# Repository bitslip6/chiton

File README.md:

# Chiton · Wide-Angle 940 nm Time-of-Flight Sensor for Autonomous Mobile Robots

[See the application](#see-the-application) · [Engineering highlights](#engineering-highlights) · [Run it locally](#run-on-your-desktop)

Chiton controls and processes data from the **Chiton 8-vixel, 940 nm
Time-of-Flight camera**: **270° coverage, VGA (640 × 480), and 30 fps**.
The application combines sensor control, on-device processing, live visualization,
measurements, and data export. The camera serves the browser interface directly.

Chiton runs on embedded Linux and uses C++ for camera SDK integration, image
processing, and network services. Build tools, automated tests, and deployment
bundles support development from the desktop to the camera.

*Color-mapped depth view. Colors represent distance across the scene.
Select any screenshot to view it at full size.*

## Camera platform

The camera platform combines an **i.MX8 system-on-module**, a **Sony CMOS image sensor**, and an **Analog Devices (ADI)
Time-of-Flight ASIC**. ToF imaging measures distance using emitted light and its
return, producing depth data as well as infrared intensity images.

| | Camera platform |
| --- | --- |
| Sensing | 8-vixel, 940 nm Time-of-Flight; depth and infrared intensity |
| Field of view | 270 degrees |
| Acquisition | VGA, 640 × 480 pixels at 30 frames per second |
| Compute | i.MX8 SOM running embedded Linux |
| Connectivity | Gigabit Ethernet and/or 2.4 GHz wireless |
| Extensibility | Customer C++ processing code runs on the camera through a native plugin |
| Client access | Browser UI, HTTP data exports, and persistent JPEG WebSocket streaming |

The platform supports hardware encode/decode and 30-fps data export in a variety
of formats. Processing workload, format, codec path, and network conditions
determine the delivered frame rate. The application encodes JPEGs with
**libjpeg**. Validate hardware codec operation and throughput on the target camera.

## Explore and process sensor data

Use Chiton to:

1. **Explore the scene.** Switch between depth and IR, adjust visualization, and
   inspect the camera's wide-angle view from a browser.
2. **Understand the measurements.** Select pixels or regions and inspect values,
   statistics, units, and the frame's processing state.
3. **Develop on the device.** Add customer processing through `api.so`, keeping
   frame processing close to the sensor.
4. **Integrate with other tools.** Export processed 16-bit images, JPEGs, binary
   point clouds, and OBJ vertices through documented interfaces.
5. **Develop on your desktop.** Use file-backed camera simulation and automated
   tests on a Linux development machine.

## See the application

| Grayscale view | 3D point-cloud view |
| --- | --- |
|  |  |
| Inspect the scene and selected-pixel values. | Explore the scene as spatial points and export its geometry. |

The application also supports an **unwrapped planar view**, presenting the
curved camera image as a horizontal strip. See the
[planar-view diagnostic capture](images/chiton-unwrap-dog.png).

The screenshots show the application interface and its visualization modes.
The planar capture includes development telemetry. Use controlled performance
tests to measure throughput and latency.

## Engineering highlights

| Area | Implementation |
| --- | --- |
| **Embedded camera integration** | Integrates the ADI SDK, manages capture and device-global settings, and supports framebuffer and headless operation on Linux |
| **Image processing and geometry** | Calibrates and smooths samples, renders grayscale/color images, remaps planar views, and generates point clouds |
| **On-device extensibility** | Runs customer frame-processing code through a native C++ plugin interface |
| **Networked visualization** | Serves the browser UI, streams JPEGs with bounded per-viewer buffering, and provides snapshot fallback |
| **Data integrity** | Binds metadata to snapshots, reports units and frame IDs, isolates measurement histories, and checks calibration storage |
| **Developer experience** | Provides file-backed simulation, portable ARM/x86 SIMD support, CMake/Make builds, and documented data contracts |
| **Validation and deployment** | Runs sanitizer and browser CI gates, retains failure logs, and packages versioned AArch64 bundles for operator-controlled deployment and rollback |

### How the pieces fit together

```text
ToF camera + ADI SDK          File-backed simulator
             \                         /
              +---- Capture pipeline --+
                            |
                  On-device processing
             calibration / customer plugin / rendering
                            |
              +-------------+--------------+
              |                            |
     Processed data + metadata      JPEG encoding + publication
              |                            |
     HTTP measurements/exports      WebSocket / HTTP preview
              |                            |
              +------ Browser / client ----+
```

The camera application manages the SDK and processes frames on the device.
Clients consume published data through HTTP and WebSocket interfaces. Raw data
and JPEGs retain their source-frame metadata as each processing stage completes.
Slow JPEG viewers skip intermediate frames to keep their buffers bounded.

For implementation details, see [image streaming](docs/image-streaming.md),
[measurement semantics](docs/measurements.md), and
[HTTP contracts](docs/http-contracts.md).

## Run on your desktop

Build Chiton on **Linux with a C++17 compiler**. Follow this Ubuntu/Debian
example to run the application with file-backed depth and IR inputs.

### 1. Get the source and dependencies

```sh
git clone https://github.com/bitslip6/chiton.git
cd chiton
git submodule update --init -- FunctionalPlus

sudo apt-get update
sudo apt-get install -y build-essential cmake pkg-config python3 \
  libpng-dev libjpeg-dev zlib1g-dev libi2c-dev libsimde-dev
```

Initialize the named build dependency and use CMake 3.10 or newer. You can also
supply SIMDe through a [source checkout](https://github.com/simd-everywhere/simde)
by adding `-DSIMDE_INCLUDE_DIR=/path/to/simde` to the configuration command.

### 2. Build and run

```sh
cmake -S . -B _build/desktop \
  -DUSE_ADITOF_STUB=ON \
  -DUSE_SDL2=OFF \
  -DCHITON_DEFAULT_DISPLAY=headless
cmake --build _build/desktop -j2

python3 tools/generate_stub_images.py --pattern gradient --output-dir /tmp/chiton-images
ADITOF_STUB_IR=/tmp/chiton-images/aditof-ir.bin \
ADITOF_STUB_DEPTH=/tmp/chiton-images/aditof-depth.bin \
  ./_build/desktop/chiton --display headless
```

Open **`http://localhost/`** or **`http://localhost:8080/`**, using the port that
the application reports in its startup log. The app tries port 80, then 8080;
allow it to bind to at least one available port. Stop it with **Ctrl+C**.

The generator creates a gradient for repeatable testing. It preserves existing
images by default; add `--force` to replace them.

<details>
<summary><strong>Simulator inputs, desktop preview, and Make builds</strong></summary>

Each simulator input contains exactly 640 × 480 little-endian unsigned 16-bit
samples (614,400 bytes) in headerless, row-major order. Camera samples use the
12-bit range 0–4095. The simulator repeats these images on every frame and
rejects explicitly selected files that are missing or have an incorrect size.
Measure sensor performance separately on the camera.

By default, the simulator uses `aditof-ir.bin` and `aditof-depth.bin` in the
working directory. It creates missing default files with every pixel set to 320.

For a local preview window, install `libsdl2-dev` and build separately:

```sh
cmake -S . -B _build/desktop-sdl -DUSE_ADITOF_STUB=ON -DUSE_SDL2=ON
cmake --build _build/desktop-sdl -j2
./_build/desktop-sdl/chiton --display desktop
```

Choose `auto`, `desktop`, `framebuffer`, or `headless` for the display backend.
Headless mode runs capture and network services independently of a local screen.

Alternatively, use Make:

```sh
make USE_ADITOF_STUB=1 USE_SDL2=0
./bin/chiton --display headless
```

Make outputs `bin/chiton` and isolates build variants under `_build/`.
Use `make print` to inspect configuration. Make selects native compilers by
default; pass compiler and architecture overrides explicitly.

</details>

## Connect a client or add your own processing

On a running camera, open `http://<camera-address>/`. Add `:8080` when the
startup log reports that port. The device address and wireless provisioning depend on its
installed image and configuration.

| Output | Route | Format |
| --- | --- | --- |
| Frame metadata | `/frame/camera` | JSON mode, type, dimensions, frame ID, age, and processing state |
| Processed depth or IR | `/raw/camera` | 640 × 480 unsigned 16-bit samples; response headers identify units and byte order |
| Preview image | `/image/camera` | JPEG; the selected mode controls image dimensions |
| Binary point cloud | `/pointcloud/camera` | Signed 16-bit X/Y/Z/distance records |
| OBJ point cloud | `/pointcloud_obj/camera` | ASCII vertices; coordinates divided by 6000 |

**Settings apply to every connected client.** Select cloud mode (4) before
point-cloud exports. Frame reads preserve the selected mode. The `/raw/camera`
endpoint returns processed samples that may include calibration, smoothing, and
plugin edits. Consult the [data contracts](docs/http-contracts.md) for processing
semantics, sample layouts, and units.

To wait for a newer snapshot, use `?after=<frame_id>&timeout_ms=1000` on a frame
endpoint. Ordinary reads may return 503 during a transition; newer-frame waits
return 504 on expiry, and incompatible formats return 409. Wait on the JPEG
endpoint itself when you need an encoded image—raw metadata can publish first.
Timestamps record when the host receives each frame.

### Customer processing plugins

[`api/api.cpp`](api/api.cpp) and [`api/api.h`](api/api.h) provide the example
`process_standard_frame` callback and optional `set_runlines` mapping callback.
Build the example from the repository root with **`make api`**. For the camera,
compile against its architecture and ABI and include `api.so` in the release's
resource location. Build a separate plugin binary for each target architecture.

Plugins execute trusted native code with the application's process privileges.
Their execution time contributes to the frame-processing budget. Review the
[plugin compatibility contract](docs/measurements.md), including private-copy
ownership and the legacy final-element counter, before integrating your code.

## Build and deploy to the camera

Install the **ADI SDK**, an ARM/AArch64 toolchain, and libraries compatible
with the device's Linux image before building for hardware. Select
`USE_ADITOF_STUB=OFF` in CMake or `USE_ADITOF_STUB=0` in Make.

- [Cross-build and target-library compatibility](docs/aarch64-cross-build.md)
- [Versioned application bundles, configuration, and rollback](docs/deployment-bundle.md)
- [Release process and hardware qualification checklist](docs/release-gates.md)

Deploy assets and private libraries with the executable. Preserve device
configuration/calibration and a known-good release, and stop the existing
camera owner before starting another. Run one camera-owning process at a time.

**Network boundary:** restrict access to a trusted network or protect remote
access with an authenticated TLS reverse proxy. The application relies on that
external boundary for authentication and transport security. Device-management
routes can change device state.

## Quality and validation

The live badge at the top links to the **Web release gates** workflow. GitHub
Actions runs on pushes and pull requests, with separate checks for:

- **Normal and sanitizer builds:** AddressSanitizer, UndefinedBehaviorSanitizer,
  and ThreadSanitizer headless simulator variants on Ubuntu 22.04.
- **Application contracts:** native tests and simulator HTTP checks for frames,
  measurements, exports, settings, and lifecycle behavior.
- **Browser behavior:** Chromium recovery/download checks for both shipped UI
  copies, alongside deterministic UI tests.

Run the same desktop gates locally with build dependencies, Node.js, and Chromium:

```sh
python3 tests/release_gate.py --all --output /tmp/chiton-release-checks --jobs 2
```

Use a **new output directory**. The gate stops on failed checks and retains logs.
See [focused validation commands](tests/SAFETY.md) and the
[release-gate scope](docs/release-gates.md).

**Validation scope:** desktop CI exercises software behavior with simulated
inputs. Qualify optical performance, illumination safety, hardware codecs, and
sustained network throughput on the target camera. The legacy Yocto workflows
perform checkout when you trigger them manually. The server handles ordinary
HTTP requests sequentially and runs persistent JPEG streaming through a separate
bounded reactor. The [web-server review](docs/web-server-review.md) tracks
remaining engineering work.

## Explore the repository

| Location | Contents |
| --- | --- |
| `src/`, `include/` | Camera integration, processing, display, and network services |
| `api/` | Customer frame-processing plugin example |
| `release/` | Browser assets and application resources |
| `images/` | Application screenshots |
| `tests/` | Native, HTTP, browser, and release-gate checks |
| `tools/` | Fixture generation, packaging, and development utilities |
| `docs/` | Architecture details, data contracts, deployment, and engineering notes |
| `linux/`, `devops/`, `deprecated/` | Hardware support and legacy platform material |

For display work, see [TFT refresh qualification](docs/display-refresh-benchmark.md)
and [SPI driver diagnostics](docs/spi-display-diagnostics.md).

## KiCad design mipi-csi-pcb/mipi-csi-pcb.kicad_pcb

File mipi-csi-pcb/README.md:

# mipi-csi-pcb
 # MIPI-CSI interface for Variscite EVK
 
 * Edge connector on the front, ZIF connector on the back
 * For edge connector, should use CSI_P1. CSI_P2 is not exposed for i.MX8M Mini SOM.
 * Passing MIPI Data0, Data1, CK and I2C signals.

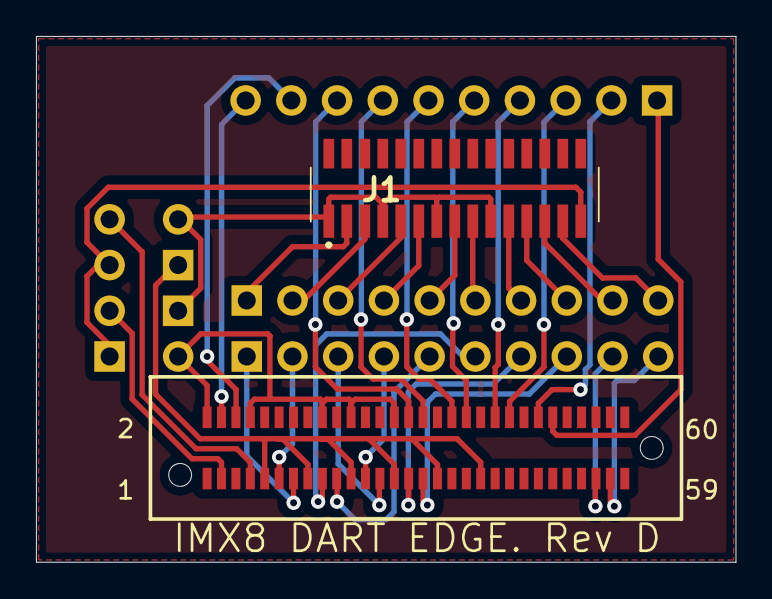
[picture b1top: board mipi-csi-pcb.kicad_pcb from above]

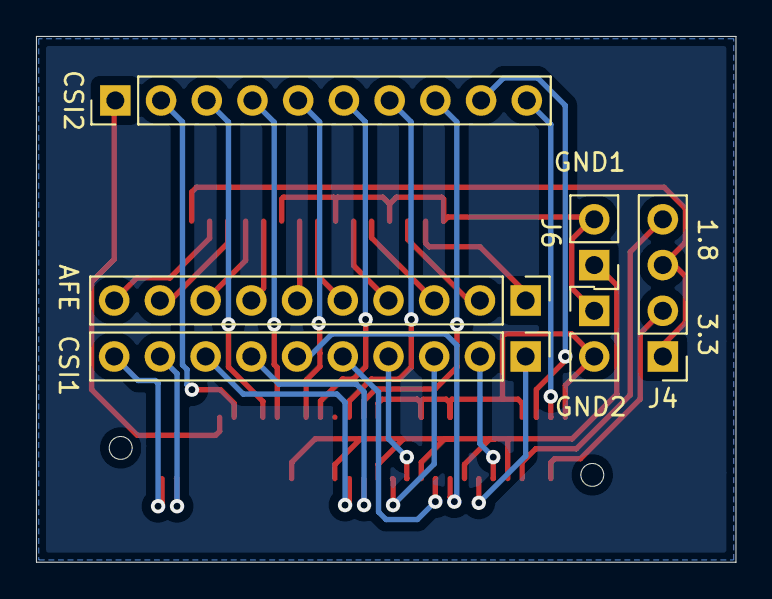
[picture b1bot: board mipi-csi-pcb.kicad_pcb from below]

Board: 2 copper layers, 38.9 x 29.2 mm, 8 parts (6 on the bottom side), 28 nets.

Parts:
AFE: AFE; PinHeader_1x10_P2.54mm_Vertical
CSI1: CSI1; PinHeader_1x10_P2.54mm_Vertical
CSI2: CSI2; PinHeader_1x10_P2.54mm_Vertical
GND2: CSI1_GND; PinHeader_1x02_P2.54mm_Vertical
IMX8 DART EDGE. Rev D: Variscite_Edge; snapeda-HSEC8-130-01-L-DV-A
J1: AFE; 117342485
J4: 3.3_1.8; PinHeader_1x04_P2.54mm_Vertical
J6: CSI2_GND; PinHeader_1x02_P2.54mm_Vertical

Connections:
/3.3: J1.15, J4.1, J4.3
/MIPI_CSI_CLK_N: AFE.5, CSI1.5, IMX8 DART EDGE. Rev D.19, J1.8
/MIPI_CSI_CLK_P: AFE.6, CSI1.6, IMX8 DART EDGE. Rev D.17, J1.9
/MIPI_CSI_DATA0_N: AFE.1, CSI1.1, IMX8 DART EDGE. Rev D.13, J1.2
/MIPI_CSI_DATA0_P: AFE.2, CSI1.2, IMX8 DART EDGE. Rev D.11, J1.3
/MIPI_CSI_DATA1_N: AFE.3, CSI1.3, IMX8 DART EDGE. Rev D.25, J1.5
/MIPI_CSI_DATA1_P: AFE.4, CSI1.4, IMX8 DART EDGE. Rev D.23, J1.6
/MIPI_CSI_DATA2_N: CSI1.8, IMX8 DART EDGE. Rev D.31
/MIPI_CSI_DATA2_P: CSI1.7, IMX8 DART EDGE. Rev D.29
/csi_p2_clk_N: CSI2.4, IMX8 DART EDGE. Rev D.42
/csi_p2_clk_P: CSI2.3, IMX8 DART EDGE. Rev D.44
/csi_p2_data0_N: CSI2.2, IMX8 DART EDGE. Rev D.48
/csi_p2_data0_P: CSI2.1, IMX8 DART EDGE. Rev D.50
/csi_p2_data1_N: CSI2.6, IMX8 DART EDGE. Rev D.36
/csi_p2_data1_P: CSI2.5, IMX8 DART EDGE. Rev D.38
/csi_p2_data2_N: CSI2.8, IMX8 DART EDGE. Rev D.30
/csi_p2_data2_P: CSI2.7, IMX8 DART EDGE. Rev D.32
/i2c4_scl: CSI2.9, IMX8 DART EDGE. Rev D.6
/i2c4_sda: CSI2.10, IMX8 DART EDGE. Rev D.4
/i2c_scl: AFE.9, CSI1.9, IMX8 DART EDGE. Rev D.55, J1.13
/i2c_sda: AFE.10, CSI1.10, IMX8 DART EDGE. Rev D.57, J1.14
GNDA: GND2.2, J1.1, J1.4, J1.7, J1.10, J6.1
GNDD: GND2.1, IMX8 DART EDGE. Rev D.9, IMX8 DART EDGE. Rev D.15, IMX8 DART EDGE. Rev D.21, IMX8 DART EDGE. Rev D.27, IMX8 DART EDGE. Rev D.33, IMX8 DART EDGE. Rev D.39
unnamed: AFE.7, J1.11
unnamed: AFE.8, J1.12
unnamed: IMX8 DART EDGE. Rev D.1, IMX8 DART EDGE. Rev D.3, J4.2
unnamed: IMX8 DART EDGE. Rev D.5, IMX8 DART EDGE. Rev D.7, J4.4
unnamed: IMX8 DART EDGE. Rev D.2, IMX8 DART EDGE. Rev D.8, IMX8 DART EDGE. Rev D.18, IMX8 DART EDGE. Rev D.22, IMX8 DART EDGE. Rev D.28, J6.2

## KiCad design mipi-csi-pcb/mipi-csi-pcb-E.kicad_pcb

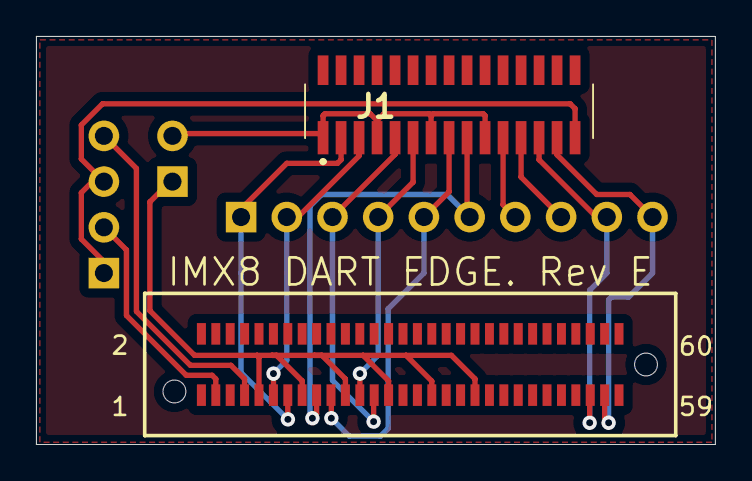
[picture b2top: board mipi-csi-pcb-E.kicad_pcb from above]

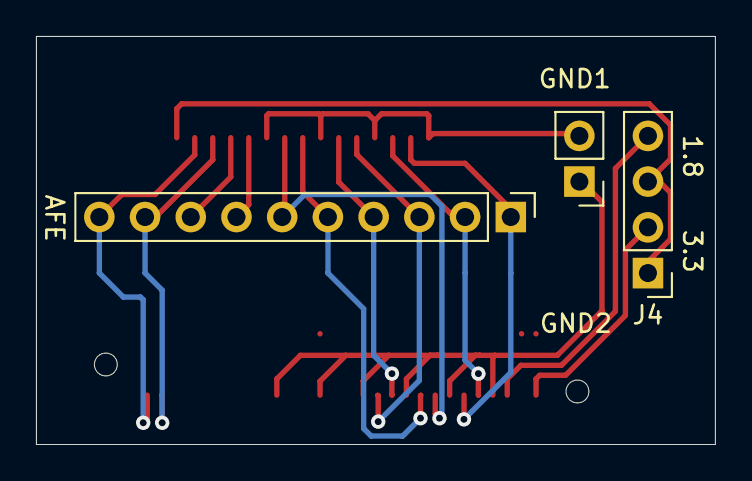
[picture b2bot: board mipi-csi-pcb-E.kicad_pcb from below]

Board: 2 copper layers, 37.7 x 22.7 mm, 5 parts (3 on the bottom side), 16 nets.

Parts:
AFE: AFE; PinHeader_1x10_P2.54mm_Vertical
GND2: CSI1_GND; PinHeader_1x02_P2.54mm_Vertical
IMX8 DART EDGE. Rev E: Variscite_Edge; snapeda-HSEC8-130-01-L-DV-A
J1: AFE; 117342485
J4: 3.3_1.8; PinHeader_1x04_P2.54mm_Vertical

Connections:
/3.3: J1.15, J4.1, J4.3
/MIPI_CSI_CLK_N: AFE.5, IMX8 DART EDGE. Rev E.19, J1.8
/MIPI_CSI_CLK_P: AFE.6, IMX8 DART EDGE. Rev E.17, J1.9
/MIPI_CSI_DATA0_N: AFE.1, IMX8 DART EDGE. Rev E.13, J1.2
/MIPI_CSI_DATA0_P: AFE.2, IMX8 DART EDGE. Rev E.11, J1.3
/MIPI_CSI_DATA1_N: AFE.3, IMX8 DART EDGE. Rev E.25, J1.5
/MIPI_CSI_DATA1_P: AFE.4, IMX8 DART EDGE. Rev E.23, J1.6
/i2c_scl: AFE.9, IMX8 DART EDGE. Rev E.55, J1.13
/i2c_sda: AFE.10, IMX8 DART EDGE. Rev E.57, J1.14
GNDA: GND2.2, J1.1, J1.4, J1.7, J1.10
GNDD: GND2.1, IMX8 DART EDGE. Rev E.9, IMX8 DART EDGE. Rev E.15, IMX8 DART EDGE. Rev E.21, IMX8 DART EDGE. Rev E.27, IMX8 DART EDGE. Rev E.33, IMX8 DART EDGE. Rev E.39
unnamed: AFE.7, J1.11
unnamed: AFE.8, J1.12
unnamed: IMX8 DART EDGE. Rev E.1, IMX8 DART EDGE. Rev E.3, J4.2
unnamed: IMX8 DART EDGE. Rev E.5, IMX8 DART EDGE. Rev E.7, J4.4
unnamed: IMX8 DART EDGE. Rev E.2, IMX8 DART EDGE. Rev E.8, IMX8 DART EDGE. Rev E.18, IMX8 DART EDGE. Rev E.22, IMX8 DART EDGE. Rev E.28

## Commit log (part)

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2020-11-06 support for different color modes
2020-11-07 formatting and logging
2020-11-07 logging
2020-11-07 fixed logging formatter
2020-11-07 cleaned
2020-11-07 standard errors and warnings
2020-11-07 warning for out of bounds check
2020-11-07 add filter to remove "outliers" from average value
2020-11-07 remove data locking
2020-11-09 adding basic timing measurement
2020-11-09 removing empty line on hsv.cpp
2020-11-09 refactoring of the depth_to_hsv for perf improvements
2020-11-09 adding missing {}
2020-11-09 updating depth_to_hsv() signature
2020-11-09 adding timing measurement and init_depth_to_hsv
2020-11-09 adapting to new depth_to_hsv() signature
2020-11-09 adding Warn_If
2020-11-09 updating debug info
2020-11-09 adjusting color_fn
2020-11-10 PR review: setting fields to empty instead of zero
2020-11-10 using TRACE instead of INFO for logging
2020-11-10 PR #114 revision
2020-11-10 update c/cxx flags
2020-11-10 required actions to set permissions and autostart after upgrade
2020-11-10 github action using cross compiler
2020-11-11 #93 , #99 - temperature monitor, warnings and shutdown
2020-11-11 script for local build and deploy to target
2020-11-11 convert to EXIT_IF
2020-11-11 clean up
2020-11-11 logging cleanup
2020-11-11 add spark line chart. switch to requestanimation frame for smooth ui updates
2020-11-11 add timer feature
2020-11-11 updated color functions
2020-11-11 cleaned up image functions
2020-11-11 add a depth to rgb8 pixel mapping func
2020-11-11 prep work for functionalizing webserver.cpp
2020-11-11 depth to color functions
2020-11-11 move color cuntions to hsv
2020-11-11 web server update
2020-11-11 remove invalid trace
2020-11-11 double buffering for jpeg transfer
2020-11-11 fix frame rate
2020-11-11 set ui ver 24
2020-11-11 revert to master
2020-11-11 revert app3.html to master
2020-11-11 update crosscompile script
2020-11-11 restore monitor_thread lost in conflict solving
2020-11-11 adding target update_json on Makefile
2020-11-11 update_json 1st version
2020-11-11 fixes for #120
2020-11-11 Update README.md
    add devops status
2020-11-11 based code base is ok for x86 and gcc 10 - #115
2020-11-11 #115 update devops names
2020-11-11 running bool -> int
2020-11-11 better debug messasge
2020-11-11 running is int
2020-11-11 logging standards
2020-11-12 update build flow #115
2020-11-12 fix noise calculation
2020-11-13 build only on *.c and *.cpp changes #115
2020-11-13 scripts to build yocto-3.1-sdk-gcc-9.3.0
2020-11-13 general error page
2020-11-13 fix double defines
2020-11-13 pause before startup waiting for low temperature
2020-11-13 update warnings and errors
2020-11-13 update logging
2020-11-15 update #115
2020-11-15 update #115 scripts
2020-11-15 update sdks in devops #115
2020-11-15 working version... need to remove prints
2020-11-16 update #115 devops
2020-11-16 update #115, reduce docker images from 12GB to 2.5: 474mb and 3.1: 559mb
2020-11-16 update #115 workflow names
2020-11-16 devops #115 - reduced intel sdk from 12gb to 192mb
2020-11-16 update readme #115
2020-11-16 command line arguments and tests
2020-11-16 add aditof_chiton.patch #115
2020-11-16 clamp color min/max values
2020-11-16 CLAMP fixes
2020-11-16 add show samples and add new log level 0
2020-11-16 new shapes and performance options
2020-11-16 new 2d point types
2020-11-16 fix off by 1 error
2020-11-16 add dependency
2020-11-16 cleaning up trash code
2020-11-16 first field of measurements is now a string
2020-11-16 small fix on Makefile
2020-11-16 u16 wfile write
2020-11-16 update cmake
2020-11-16 fix cmake #115
2020-11-17 clean up Makefile
2020-11-17 config.json: vixel field is string now
2020-11-17 removing prints and adding bkp file
2020-11-17 reducing redundant code
2020-11-17 removing prints
2020-11-17 planar coordinates
2020-11-17 LCD properly flipped
2020-11-18 fix chiton for devtool #115
2020-11-22 utils function for logs capturing
2020-11-22 wiring for debug files download feature
2020-11-22 adding button to download debug files
2020-11-22 testing backtrace printing
2020-11-22 entry point for signal handler on main
2020-11-23 methods for log grabbing
2020-11-23 WebUI code for debug targz downloading
2020-11-23 adding wiring for file download
2020-11-24 redirect_output without arguments
2020-11-24 redirect_output entry point on main.cpp
2020-11-24 planar code
2020-11-30 adding utils::clamp impl
2020-11-30 stoi replaced by utils::clamp
2020-11-30 vixel id as string
2020-11-30 adapting to vixel as string
2020-11-30 saving stoi on 32 bits integer type
2020-11-30 changing clamp interval to 32 bits
2020-12-01 new data repository
2020-12-01 syntax error
2020-12-01 add width calculatin and locking
2020-12-01 add new core functions
2020-12-01 improved waiting
2020-12-01 refactored data source
2020-12-01 latest mapping functions
2020-12-01 updated shape functions
2020-12-01 syntax error fix
2020-12-01 add 0 white value and raw value support
2020-12-01 refactored data source and image calibration / calculation
2020-12-01 updated functions
2020-12-01 refactored planar and polar coordinate
2020-12-01 latest processor changes
2020-12-01 remove console log
2020-12-02 clamp code on utils.hpp
2020-12-02 PR review
2020-12-02 removing commented utils:clamp
2020-12-02 added support for angle - vixel mapping
2020-12-02 fixing segfault when console_log is missing
2020-12-04 adapting to fw json
2020-12-04 filling releases dropdown list from php
2020-12-04 fixing segfault on software_fn
2020-12-07 getting releases from robotserver
2020-12-07 update_json now supports rage radian_min and radian_max
2020-12-07 adding upgrade.sh to git
2020-12-07 removing debug prints
2020-12-09 bug fixes
2020-12-10 adding toggle button
2020-12-11 setAutocalibration
2020-12-11 debug folder named as chitondebug
2020-12-14 gain merge fade
2020-12-15 adding square colors and mocked avg function
2020-12-16 wiring: update json with calibrated data
2020-12-16 backend for calibration update
2020-12-16 impl of utils::update_vixel_json
2020-12-16 updates for square painting
2020-12-28 calibration_status enum definition
2020-12-28 is_calibration_enabled flag
2020-12-28 autocalibration functions on utils
2020-12-28 autocalibration loop on main
2020-12-28 wiring autocalibration backend
2020-12-28 autocalibration webUI
2021-01-04 near and far calibration on GOPTS
2021-01-04 adding vixel_calibration_status initialization
2021-01-04 API on settings.cpp for autocal
2021-01-04 formating output on main.cpp for autocal
2021-01-04 adding wiring for autocalibration
2021-01-04 Update changelog.html
    remove old javascript
2021-01-04 constants for number of vixel and calibration distances
2021-01-04 update_calibration_on_json implementation
2021-01-04 adding utils::update_calibration_on_json on main
2021-01-05 new macros for far and near distances
2021-01-05 fixing issue
2021-01-06 yocto 3.2 build scripts and layer configuration
2021-01-06 update gitignore
2021-01-07 removing useless function
2021-01-07 gcc10 on qemu console
2021-01-07 disable outdated devops
2021-01-07 add missing chiton and glog recipes
2021-01-08 new drawing
2021-01-08 updating cal status
2021-01-14 headers for release 029
2021-01-14 setup files
2021-01-14 reset empty color
2021-01-14 add slam output
2021-01-14 add slam and gain output formats
2021-01-14 add display output
2021-01-14 debugging and remove radian_min/max
2021-01-14 support latest command output
2021-01-14 debugging output
2021-01-14 input filtering
2021-01-15 build scripts
2021-01-15 update makefile to gcc10
2021-01-15 scripts to build SDK
2021-01-15 update makefile
2021-01-15 sdk install script
2021-01-15 removing useless code from utils
2021-01-15 changing height of autocalibration squares on backend
2021-01-15 removing useless code and new square update proc
2021-01-15 removing useless code on settings.cpp
2021-01-15 adding autocalibration interval feature
2021-01-15 install to target script
2021-01-15 reset autocalibration status
2021-01-19 adding comments on main.cpp
2021-01-19 TEMP: calibration using one pixel only
2021-01-19 network options added to the UI
2021-01-19 wiring network option
2021-01-19 wiring on backend for gateway changing
2021-01-21 update steps
2021-01-22 exposing calculate_circle_point on gfx
2021-01-22 utils distance on polar image
2021-01-22 dev feature - radius input
2021-01-22 backend for radius input
2021-01-22 calc dist with polar coordinates
2021-01-22 tracking
2021-01-23 fixing vixel_index counting
2021-01-23 renamings
2021-01-23 setting default radius 236
2021-01-23 gain criteria and renamings
2021-01-26 adding cal squares to the radial view
2021-01-28 support for dl open
2021-01-28 add support for quad samples
2021-01-28 fix touchscreen inversion
2021-01-28 move to FPS delay, switch from planar to polar default
2021-01-28 simplify error log collection
2021-01-28 supoport for reloading api...
2021-01-28 support eth and lwan
2021-01-28 fix i2c code
2021-01-28 distance as float
2021-01-28 api support
2021-01-28 support quad calibration and api
2021-01-28 add quad mapping
2021-01-28 version number on tft app
2021-01-31 updating square area
2021-02-01 cmds for network routing wlan0 and eth0
2021-02-02 checking if network interface exists
2021-02-02 updating gateway change methods
2021-02-03 mashup
2021-02-03 changing beta 1st version
2021-02-04 in progress
2021-02-05 changing data type
2021-02-08 fixing autocal factor - 1.46
2021-02-08 fixing initial radius value
2021-02-11 changing autocalibration tolerance from 2 to 3
    changing autocalibration
2021-02-13 fixing upgrade from 25 to 27
2021-02-13 adding systemctl restart
2021-02-16 center offset on the web UI
2021-02-17 fixing upgrade process
2021-02-17 cleaning up update_json.cpp
2021-02-19 merging...
2021-02-20 testing i2c register writing
2021-02-20 changing beta gain value
2021-02-23 refresh crosshair
2021-02-23 missing refresh call
2021-02-24 fetch frame format
2021-02-24 auto calibration
2021-02-24 auto-calibration
2021-02-25 reading not failing, but wrong value
2021-02-25 removing dead code
2021-02-26 first i2c read version
2021-02-26 passed-by-reference parameter
2021-02-26 fix vixel merging for new math
2021-02-26 removing UI trigger used for i2c rw tests
2021-02-26 removing dead code and replacing cout
2021-02-26 suggested refactor, untested
2021-03-01 refactor + debug code
2021-03-01 removing debug ui
2021-03-01 testing mem leakage of uniqueptr on i2c_smbus_format
2021-03-01 refactoring i2c_afe_open
2021-03-02 fixing messages and descriptions
2021-03-03 add missing close(fd) calls
2021-03-03 i2c-tools support and fixing repos hashes
2021-03-04 removing code to avoid conflicts
2021-03-05 update Makefile according to the new build system
2021-03-05 processing along each radial angle, inside -> out
2021-03-05 fix segfault on i2c_write and console.log on webui
2021-03-05 removing hardcoded reg address
2021-03-05 removing cout
2021-03-05 fix y compensation
2021-03-06 fixing bad merge
2021-03-07 reviews
2021-03-08 refreshing X/Y Label
2021-03-08 fixing warnings
2021-03-09 Missing cast
2021-03-10 latest
2021-03-10 latest config file
2021-03-10 compile issues
2021-03-12 updating data methods
2021-03-12 double to float on metrics of utils
2021-03-12 metrics for both square and point are now unified for the UI
2021-03-12 removing typos and couts
2021-03-12 empty
2021-03-12 reverting accidental commits
2021-03-17 fix debug download code and remove deal standard deviation code
2021-03-17 calc standard deviation
2021-03-17 add support for merging from/to any version
2021-03-17 fixes for color modes
2021-03-17 standard deviation fixes
2021-03-17 fixes for standard deviation
2021-03-17 fixes for standard deviation and debug files
2022-06-07 moved murillo scripts to correct location
2022-06-07 import of C++ api
2022-06-07 import jena rover arduino sketch
2022-06-07 latest web server files (release 094)
2022-06-07 import required .so files
2022-06-07 required so and build scripts
2022-06-07 updated includes
2022-06-07 new includes
2022-06-07 updated source code
2022-06-07 new library includes
2022-06-07 add build scripts for gcc 10 cross compiler
2022-06-07 removed un-needed binaries
2022-06-07 removed lvgl
2022-06-07 old make
2022-06-07 latest makefile
